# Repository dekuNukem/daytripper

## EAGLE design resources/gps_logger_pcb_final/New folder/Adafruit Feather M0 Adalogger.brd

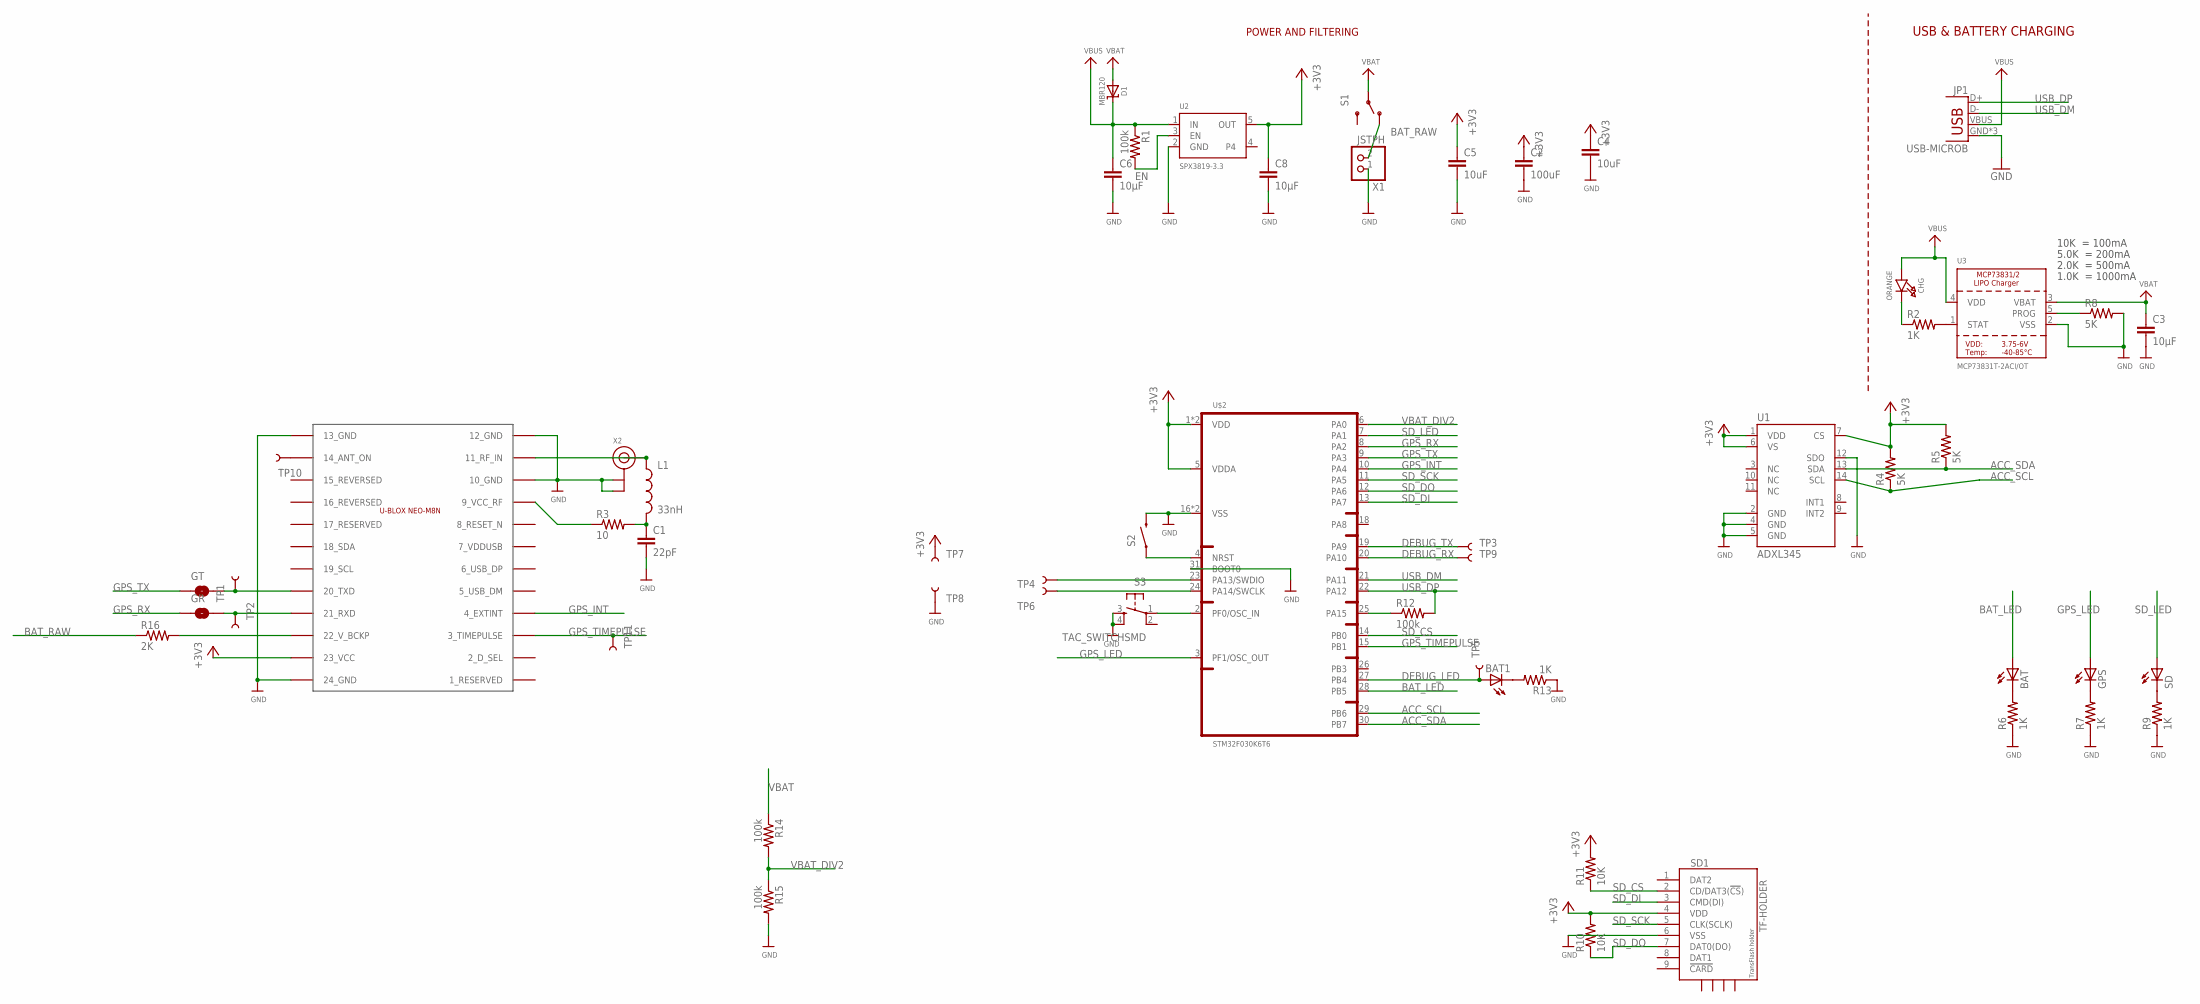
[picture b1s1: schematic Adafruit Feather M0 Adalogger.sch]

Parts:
BAT, BAT1: LEDCHIPLED_0805; CHIPLED_0805
C1: 22pF; 0805
C2: 100uF; 1210
C3, C6, C8: 10µF; 0805
C4, C5: 10uF; 0805
CHG: ORANGE; CHIPLED_0805_NOOUTLINE
D1: MBR120; SOD-123
DEKU1: UBLOX_NEO-M8N
GPS: LEDCHIPLED_0805; CHIPLED_0805
GR: JUMPER-PAD-2-NO; PAD-JUMPER-2-NO_NO_SILK
GT: JUMPER-PAD-2-NO; PAD-JUMPER-2-NO_NO_SILK
JP1: USB-MICROB
L1: 33nH; 0805
R1, R12, R14, R15: 100k; 0805
R2, R6, R7, R9, R13: 1K; 0805
R3: 10; 0805
R4, R5, R8: 5K; 0805
R10, R11: 10K; 0805
R16: 2K; 0805
S1: SWITCH-SPDT-SMD-A; SWITCH-SPST-SMD-A
S2: SWITCH-MOMENTARY-2TURTLE; KMR2
S3: TAC_SWITCHSMD; TACTILE-SWITCH-SMD
SD: LEDCHIPLED_0805; CHIPLED_0805
SD1: TF-HOLDER; TF-PULL
TP1, TP2, TP3, TP4, TP5, TP6, TP7, TP8, TP9, TP10, TP11: TEST-POINT3X5; PAD.03X.05
U1: ADXL345; LGA14
U2: SPX3819-3.3; SOT23-5
U3: MCP73831T-2ACI/OT; SOT23-5
U$2: STM32F030K6T6; TQFP32-08
X1: JSTPH; JSTPH2
X2: ANTENNA_U.FL; U.FL

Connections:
+3V3: C2.1, C4.1, C5.1, C8.1, DEKU1.23_VCC, R4.2, R5.2, R10.2, R11.2, SD1.4 (VDD), TP7.P$1, U1.1 (VDD), U1.6 (VS), U1.7 (CS), U2.5 (OUT), U$2.1 (VDD), U$2.5 (VDDA), U$2.17 (VDD)
ACC_SCL: R4.1, U1.14 (SCL), U$2.29 (PB6)
ACC_SDA: R5.1, U1.13 (SDA), U$2.30 (PB7)
BAT_LED: BAT.A, U$2.28 (PB5)
BAT_RAW: R16.1, S1.1 (O), X1.2
DEBUG_LED: BAT1.A, TP5.P$1, U$2.27 (PB4)
DEBUG_RX: TP9.P$1, U$2.20 (PA10)
DEBUG_TX: TP3.P$1, U$2.19 (PA9)
EN: R1.2, U2.3 (EN)
GND: C1.2, C2.2, C3.2, C4.2, C5.2, C6.2, C8.2, DEKU1.10_GND, DEKU1.12_GND, DEKU1.13_GND, DEKU1.24_GND, JP1.GND, JP1.MT1 (GND), JP1.MT2 (GND), R6.1, R7.1, R8.2, R9.1, R13.1, R15.2, S2.3 (2), S3.3, S3.4, SD1.6 (VSS), TP8.P$1, U1.2 (GND), U1.4 (GND), U1.5 (GND), U1.12 (SDO), U2.2 (GND), U3.2 (VSS), U$2.16 (VSS), U$2.31 (BOOT0), U$2.32 (VSS), X1.1, X2.1 (GND), X2.2 (GND)
GPS_INT: DEKU1.4_EXTINT, U$2.10 (PA4)
GPS_LED: GPS.A, U$2.3 (PF1/OSC_OUT)
GPS_RX: GR.1, U$2.8 (PA2)
GPS_TIMEPULSE: DEKU1.3_TIMEPULSE, TP11.P$1, U$2.15 (PB1)
GPS_TX: GT.1, U$2.9 (PA3)
unnamed: CHG.C, R2.1
unnamed: DEKU1.20_TXD, GT.2, TP1.P$1
unnamed: R2.2, U3.1 (STAT)
unnamed: R8.1, U3.5 (PROG)
unnamed: DEKU1.21_RXD, GR.2, TP2.P$1
unnamed: R12.1, U$2.25 (PA15)
unnamed: S2.1, U$2.4 (NRST)
unnamed: DEKU1.11_RF_IN, L1.1, X2.3 (SIGNAL)
unnamed: DEKU1.9_VCC_RF, R3.1
unnamed: C1.1, L1.2, R3.2
unnamed: BAT.C, R6.2
unnamed: GPS.C, R7.2
unnamed: R9.2, SD.C
unnamed: S3.1, U$2.2 (PF0/OSC_IN)
unnamed: BAT1.C, R13.2
unnamed: DEKU1.22_V_BCKP, R16.2
unnamed: DEKU1.14_ANT_ON, TP10.P$1
SD_CS: R11.1, SD1.2 (CD/DAT3(!CS!)), U$2.14 (PB0)
SD_DI: SD1.3 (CMD(DI)), U$2.13 (PA7)
SD_DO: R10.1, SD1.7 (DAT0(DO)), U$2.12 (PA6)
SD_LED: SD.A, U$2.7 (PA1)
SD_SCK: SD1.5 (CLK(SCLK)), U$2.11 (PA5)
SWCLK: TP6.P$1, U$2.24 (PA14/SWCLK)
SWDIO: TP4.P$1, U$2.23 (PA13/SWDIO)
USB_DM: JP1.D-, U$2.21 (PA11)
USB_DP: JP1.D+, R12.2, U$2.22 (PA12)
VBAT: C3.1, D1.A, R14.1, S1.2, U3.3 (VBAT)
VBAT_DIV2: R14.2, R15.1, U$2.6 (PA0)
VBUS: C6.1, CHG.A, D1.C, JP1.VBUS, R1.1, U2.1 (IN), U3.4 (VDD)

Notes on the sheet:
POWER AND FILTERING
10K = 100mA
5.0K = 200mA
2.0K = 500mA
1.0K = 1000mA
USB & BATTERY CHARGING

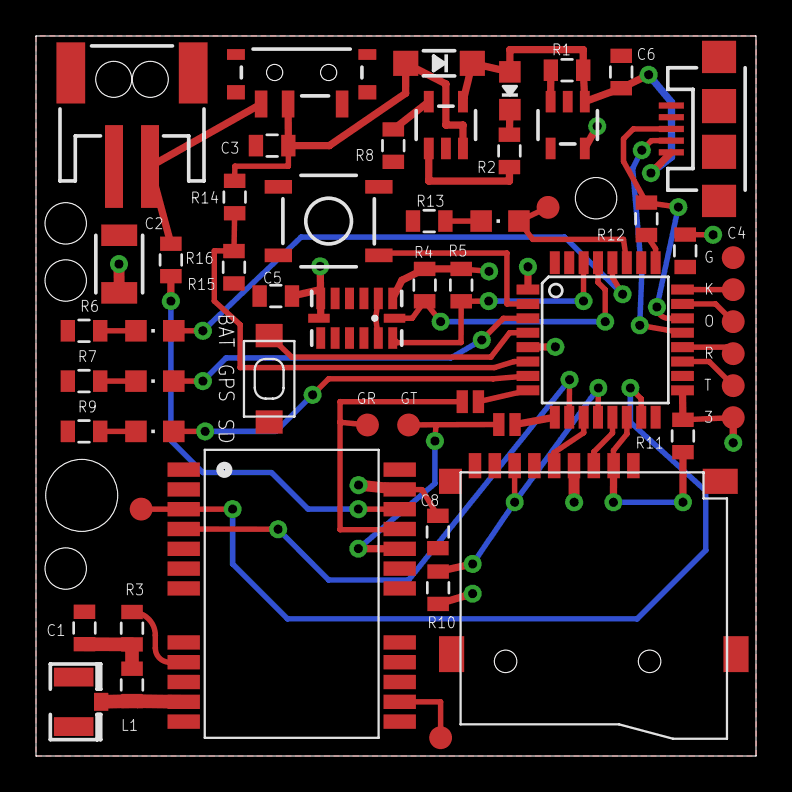
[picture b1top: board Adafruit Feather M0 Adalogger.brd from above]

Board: 2 copper layers, 40.0 x 40.0 mm, 55 parts (0 on the bottom side), 44 nets.

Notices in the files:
parts and their libraries:
microbuilder: This work is placed in the public domain, and may be freely used for commercial and non-commercial work with the following conditions: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
SparkFun-Passives: Licensing: Creative Commons ShareAlike 4.0 International - https://creativecommons.org/licenses/by-sa/4.0
